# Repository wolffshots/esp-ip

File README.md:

# ESP32 WiFi Network Interface Bridge

This project is a hardware solution that leverages the power of the ESP32 to bridge local communication interfaces, such as serial and (in the future) I2C, to a WiFi network. It allows devices with traditional communication interfaces to be accessed and controlled over WiFi.

## Features

- **Interface Bridging**: Convert and expose devices using:
  - Serial interface (current implementation)
  - I2C interface (planned for future releases)
  
- **WiFi Connectivity**:
  - Connect to an existing WiFi network.
  - Broadcast its own Access Point (AP) for direct connections.

- **Status Indicators**:
  - **Serial Communication**:
    - RX LED: Lights up when the device receives data.
    - TX LED: Lights up when the device transmits data.
  - **WiFi Indicators**:
    - Connection LED: Lights up when the device is connected to an external WiFi.
    - AP LED: Lights up when the device is broadcasting its own Access Point.

## Hardware Design

- Designed in KiCad.
- ESP32-WROOM-32U as the main microcontroller.

## Getting Started

### Prerequisites

- KiCad for viewing and editing the design files.
- A compatible power source for the board.

### Setup

1. **Power the board**: Connect the board to a suitable power source.
2. **Connection**:
    - For Serial: Connect your serial device to the designated serial port.
    - For I2C (Future): Connect your I2C device to the designated I2C connectors.
3. **WiFi**:
    - Connect to an existing WiFi: Set the credentials in the firmware and upload to the ESP32.
    - Use as AP: The board will automatically broadcast its AP if it fails to connect to the saved networks.

### Configuration

Details about how users can configure the firmware for specific WiFi networks, adjust baud rates for serial communication, or other configuration details.

## Future Enhancements

- Integration of the I2C interface.
- Firmware updates over the air.

## Contribute

We welcome contributions! Please read the [CONTRIBUTING.md](./CONTRIBUTING.md) for details on submitting pull requests to us.

## License

This project is licensed under the XYZ License - see the [LICENSE.md](./LICENSE.md) file for details.

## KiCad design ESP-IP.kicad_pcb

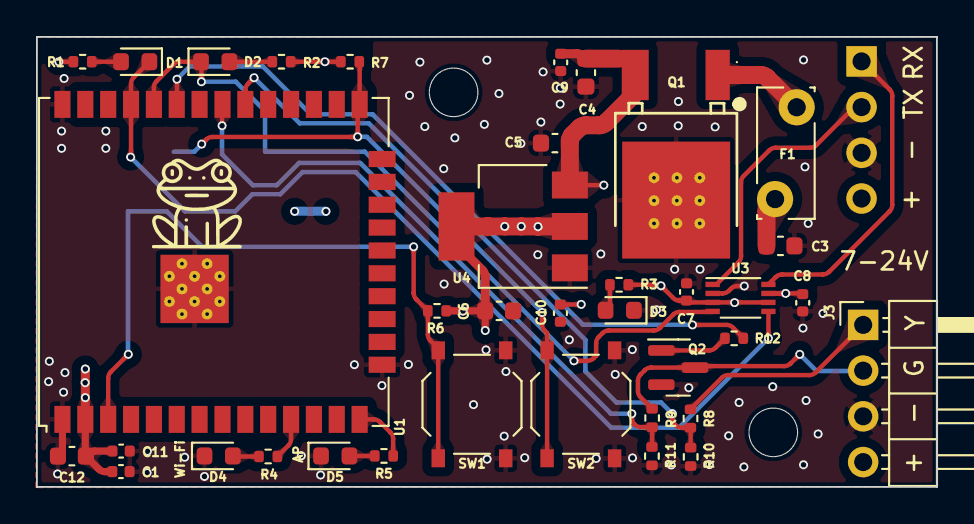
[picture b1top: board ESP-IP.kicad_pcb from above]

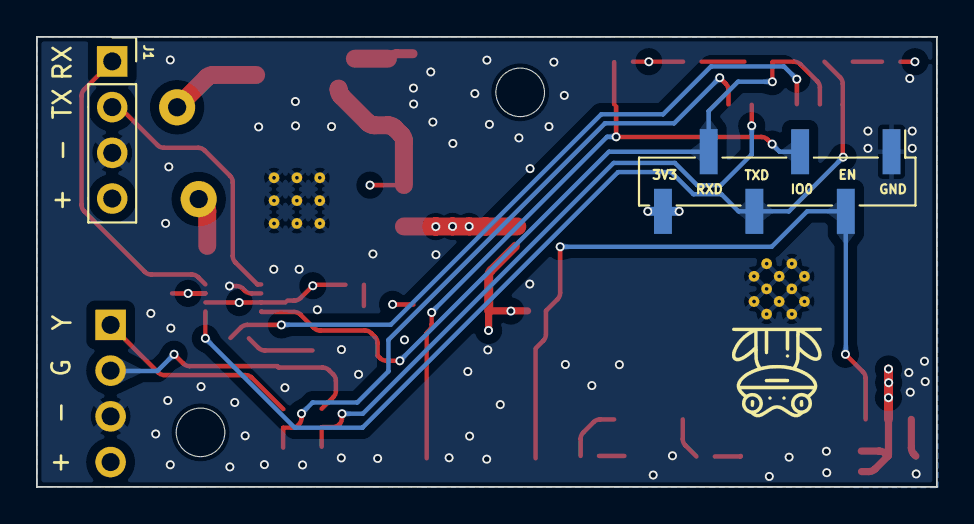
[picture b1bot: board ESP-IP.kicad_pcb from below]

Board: 4 copper layers, 50.0 x 25.0 mm, 41 parts (2 on the bottom side), 24 nets.

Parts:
C1, C7, C8, C9, C10: 100nF; C_0402_1005Metric
C3, C4, C5, C6, C12: 10uF; C_0603_1608Metric
C11: 4.7uF; C_0402_1005Metric
D1, D2, D3, D4, D5: LED; LED_0603_1608Metric
F1: 250V 80mA; Fuse_Bourns_MF-RG300
H1, H2: MountingHole; MountingHole_2.7mm_M2.5
J1: Serial and power; PinSocket_1x04_P2.54mm_Vertical
J2: Programming Pads; PinHeader_1x06_P2.54mm_Vertical_SMD_Pin1Left
J3: Comms and power; PinHeader_1x04_P2.54mm_Horizontal
Q1: L78M05ABDT-TR; TO-252-2_L6.5-W6.1-P4.58-LS10.0-TL
Q2: MMBT5551L; SOT-23
R1, R2, R3, R4, R5, R12: 1K; R_0402_1005Metric
R6, R7, R10, R11: 10K; R_0402_1005Metric
R8, R9: 33K; R_0402_1005Metric
SW1, SW2: SW_Push; SW_Push_1P1T_XKB_TS-1187A
U1: ESP32-WROOM-32U; ESP32-WROOM-32UE
U3: TXS0102DCU; VSSOP-8_2.3x2mm_P0.5mm
U4: AMS1117-3.3; SOT-223-3_TabPin2

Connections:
+3V3: C1.1, C6.1, C7.1, C10.1, C11.1, C12.1, J2.6, R1.1, R2.1, R3.1, R6.2, R7.2, U1.2 (VDD), U3.3 (VCCA), U3.6 (OE), U4.2 (VO)
+5V: C4.1, C5.1, C8.1, C9.1, Q1.3 (OUT), U3.7 (VCCB), U4.3 (VI)
+BATT: C3.1, F1.1, J1.4, J3.4
AP_STATUS: R5.1, U1.14 (IO12)
DSC_CLOCK: R8.2, R10.2, U1.30 (IO18)
DSC_GREEN: J3.2, Q2.3 (C), R9.1
DSC_READ: R9.2, R11.2, U1.31 (IO19)
DSC_WRITE: R12.2, U1.33 (IO21)
DSC_YELLOW: J3.1, R8.1
EN: J2.2, R6.1, SW1.1, U1.3 (EN)
GND: C1.2, C3.2, C4.2, C5.2, C6.2, C7.2, C8.2, C9.2, C10.2, C11.2, C12.2, D3.1 (K), D4.1 (K), D5.1 (K), J1.3, J2.1, J3.3, Q1.4 (GND), Q2.2 (E), R10.1, R11.1, SW1.2, SW2.2, U1.1 (GND), U1.15 (GND), U1.38 (GND), U1.39 (GND), U3.2 (GND), U4.1 (GND)
IO0: J2.3, R7.1, SW2.1, U1.25 (IO0)
unnamed: D1.2 (A), R1.2
unnamed: D2.2 (A), R2.2
unnamed: D3.2 (A), R3.2
unnamed: D4.2 (A), R4.2
unnamed: D5.2 (A), R5.2
unnamed: F1.2, Q1.1 (IN)
unnamed: Q2.1 (B), R12.1
RX_ESP: D2.1 (K), J2.5, U1.34 (RXD0/IO3), U3.4 (A2)
RX_OUT: J1.1, U3.8 (B1)
TX_ESP: D1.1 (K), J2.4, U1.35 (TXD0/IO1), U3.5 (A1)
TX_OUT: J1.2, U3.1 (B2)
WIFI_STATUS: R4.1, U1.11 (IO26)

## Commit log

2023-09-25 chore: initial commit
2023-09-25 doc: add initial docs
2023-09-25 doc: add example images
2023-09-25 feat: moving around bits and bobs
2023-09-25 my suggested board layout, includes schematic fixes, part number allocation and PCB, routing TBD
2023-09-25 fixing text mirrored
2023-09-26 chore: switch header back for serial and standardise labels
2023-09-26 chore: pull previous pcb in
2023-09-26 chore: switch back to socket for serial
2023-09-26 docs: update images
2023-09-26 chore: initial routing
2023-09-26 chore: swap labels of rx and tx on pin socket
2023-09-26 FEAT: ADD FROG
2023-09-26 cleaned up routing and minor PCB changes
2023-09-27 chore: switch rx and tx out
2023-09-27 chore: drop some vias and refill
2023-09-27 chore: remove disclaimer
